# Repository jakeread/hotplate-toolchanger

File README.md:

## Hotplate Toolchanger 

This is the hardware (and firmware) repo for the hotplate, an automatic, fully printable toolchanger for cnc machines. It's ostensibly part of the [clank machine platform](https://clank.tools/tools), but you could probably stick it on anything. Or reference the design patterns, and stick the idea on anything. 

Read the [dev log](log/hotplate-log.md) for updates, and you can find the [most up to date CAD in /cad](cad). Associated circuits are in [/circuit](circuit) and their firmwares in [/firmware](firmware). Some of the firmware stuff is still private (submodules) so cloning might be troublesome at the moment, just download the zip. 

More extensive documentation is [online at clank.tools/tools](https://clank.tools/tools) !

This repo is mirrored [on github](https://github.com/jakeread/hotplate-toolchanger/) and the [cba internal gitlab](https://gitlab.cba.mit.edu/jakeread/hotplate-toolchanger/).

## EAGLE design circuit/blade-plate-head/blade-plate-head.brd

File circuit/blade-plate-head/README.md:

## Hotplate Blade Head 

This circuit is integrated on the toolchanger, it contains hardware to actuate a standard servo and connects to [OSAP](https://gitlab.cba.mit.edu/jakeread/osap) systems over the [UCBus](https://gitlab.cba.mit.edu/jakeread/ucbus) PHY. 

An eagle project is here in this folder...

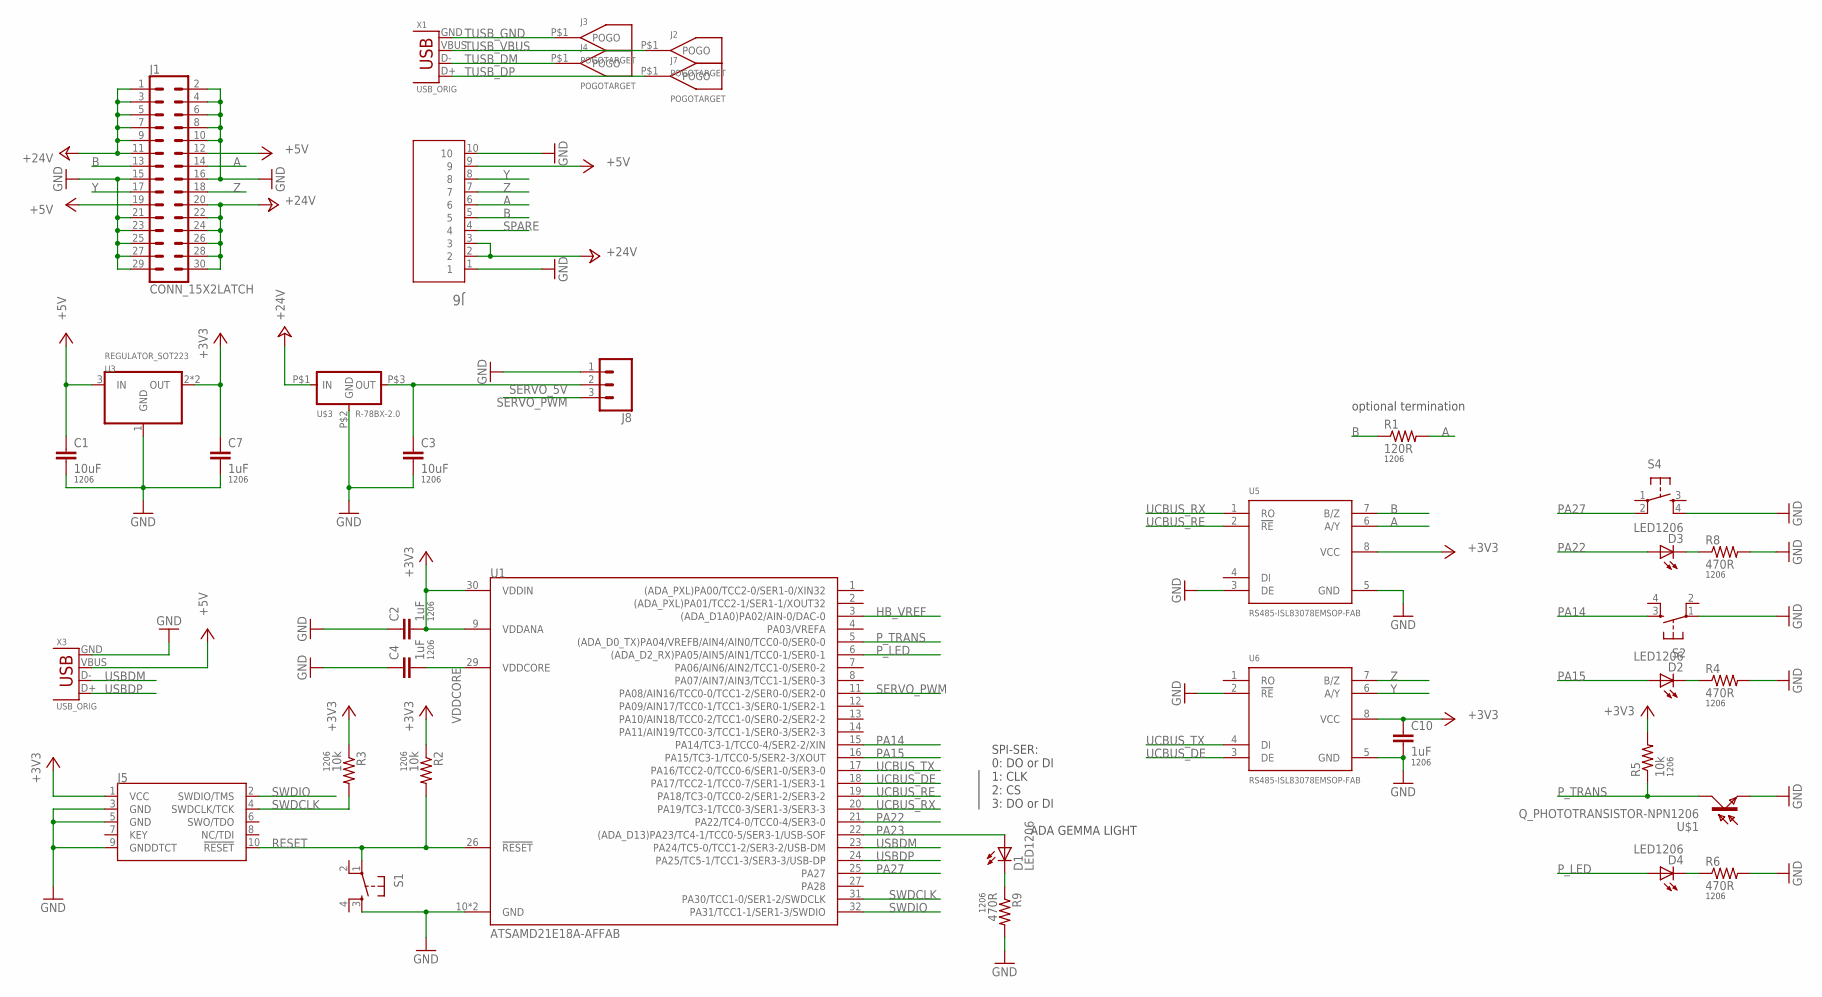
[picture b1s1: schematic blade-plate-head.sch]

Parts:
C1, C3: 10uF; 1206
C2, C4, C7, C10: 1uF; 1206
D1, D2, D3, D4: LED1206
J1: CONN_15X2LATCH; 2X15-SHROUDED_LATCH
J2, J3, J4, J7: POGOTARGET; POGO_TARGET
J5: CORTEX_JTAG_DEBUG_PTH_NS; 2X5-PTH-1.27MM-NO_SILK
J6: BLADE_10P_SCKT_1-1674231-1; TE_1-1674231-1
J8: CONN_03LOCK_NO_SILK; 1X03_LOCK_NO_SILK
R1: 120R; 1206
R2, R3, R5: 10k; 1206
R4, R6, R8, R9: 470R; 1206
S1, S2, S4: SW_SWITCH_TACTILE_6MM6MM_SWITCH; 6MM_SWITCH
U1: ATSAMD21E18A-AFFAB; TQFP-32-FAB
U3: REGULATOR_SOT223; SOT223
U5, U6: RS485-ISL83078EMSOP-FAB; 8-MSOP-FAB
U$1: Q_PHOTOTRANSISTOR-NPN1206; OP1206
U$3: R-78BX-2.0
X1, X3: USB_ORIG; DX4R005HJ5

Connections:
+3V3: C2.2, C7.1, C10.1, J5.1 (VCC), R2.1, R3.1, R5.2, U1.9 (VDDANA), U1.30 (VDDIN), U3.2 (OUT), U3.4 (OUT), U5.8 (VCC), U6.8 (VCC)
+5V: C1.1, J1.12, J1.19, J6.9, U3.3 (IN), X3.VBUS
+24V: J1.1, J1.3, J1.5, J1.7, J1.9, J1.11, J1.20, J1.22, J1.24, J1.26, J1.28, J1.30, J6.2, J6.3, U$3.P$1 (IN)
A: J1.14, J6.6, R1.2, U5.6 (A/Y)
B: J1.13, J6.5, R1.1, U5.7 (B/Z)
GND: C1.2, C2.1, C3.2, C4.1, C7.2, C10.2, J1.2, J1.4, J1.6, J1.8, J1.10, J1.15, J1.16, J1.21, J1.23, J1.25, J1.27, J1.29, J5.3 (GND), J5.5 (GND), J5.9 (GNDDTCT), J6.1, J6.10, J8.1, R4.2, R6.2, R8.2, R9.2, S1.3 (S), S2.1, S4.4 (S1), U1.10 (GND), U1.28 (GND), U3.1 (GND), U5.3 (DE), U5.5 (GND), U6.2 (!RE), U6.5 (GND), U$1.EMITTER (E), U$3.P$2 (GND), X3.GND
HB_VREF: U1.3 ((ADA_D1A0)PA02/AIN-0/DAC-0)
unnamed: D3.2 (C), R8.1
unnamed: D2.2 (C), R4.1
unnamed: D4.2 (C), R6.1
unnamed: D1.2 (C), R9.1
PA14: S2.3 (S), U1.15 (PA14/TC3-1/TCC0-4/SER2-2/XIN)
PA15: D2.1 (A), U1.16 (PA15/TC3-1/TCC0-5/SER2-3/XOUT)
PA22: D3.1 (A), U1.21 (PA22/TC4-0/TCC0-4/SER3-0)
PA23: D1.1 (A), U1.22 ((ADA_D13)PA23/TC4-1/TCC0-5/SER3-1/USB-S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)
PA27: S4.2 (P1), U1.25 (PA27)
P_LED: D4.1 (A), U1.6 ((ADA_D2_RX)PA05/AIN5/AIN1/TCC0-1/SER0-1)
P_TRANS: R5.1, U1.5 ((ADA_D0_TX)PA04/VREFB/AIN4/AIN0/TCC0-0/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), U$1.COLLECTOR (C)
RESET: J5.10 (!RESET), R2.2, S1.1, U1.26 (!RESET)
SERVO_5V: C3.1, J8.2, U$3.P$3 (OUT)
SERVO_PWM: J8.3, U1.11 (PA08/AIN16/TCC0-0/TCC1-2/SER0-0/SER2-0)
SPARE: J6.4
SWDCLK: J5.4 (SWDCLK/TCK), R3.2, U1.31 (PA30/TCC1-0/SER1-2/SWDCLK)
SWDIO: J5.2 (SWDIO/TMS), U1.32 (PA31/TCC1-1/SER1-3/SWDIO)
TUSB_DM: J4.P$1, X1.D-
TUSB_DP: J7.P$1, X1.D+
TUSB_GND: J3.P$1, X1.GND
TUSB_VBUS: J2.P$1, X1.VBUS
UCBUS_DE: U1.18 (PA17/TCC2-1/TCC0-7/SER1-1/SER3-1), U6.3 (DE)
UCBUS_RE: U1.19 (PA18/TC3-0/TCC0-2/SER1-2/SER3-2), U5.2 (!RE)
UCBUS_RX: U1.20 (PA19/TC3-1/TCC0-3/SER1-3/SER3-3), U5.1 (RO)
UCBUS_TX: U1.17 (PA16/TCC2-0/TCC0-6/SER1-0/SER3-0), U6.4 (DI)
USBDM: U1.23 (PA24/TC5-0/TCC1-2/SER3-2/USB-DM), X3.D-
USBDP: U1.24 (PA25/TC5-1/TCC1-3/SER3-3/USB-DP), X3.D+
VDDCORE: C4.2, U1.29 (VDDCORE)
Y: J1.17, J6.8, U6.6 (A/Y)
Z: J1.18, J6.7, U6.7 (B/Z)

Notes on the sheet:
SPI-SER: 0: DO or DI 1: CLK 2: CS 3: DO or DI
ADA GEMMA LIGHT
optional termination

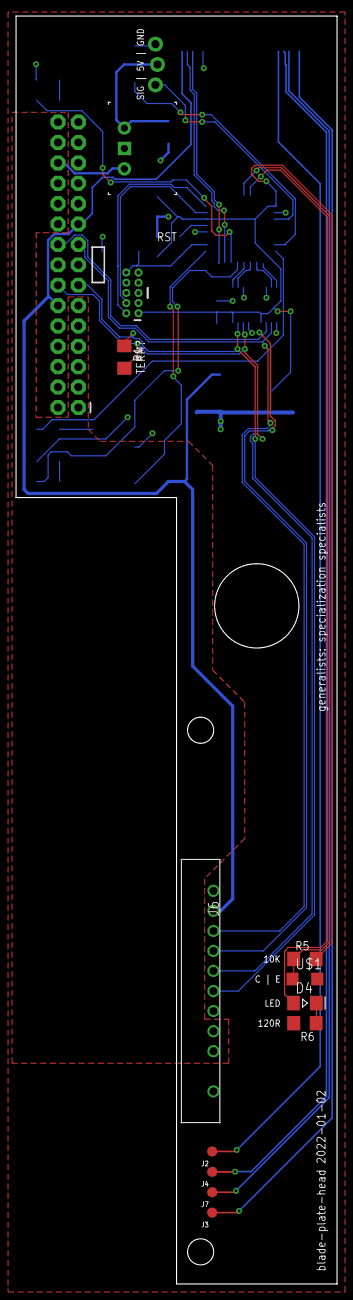
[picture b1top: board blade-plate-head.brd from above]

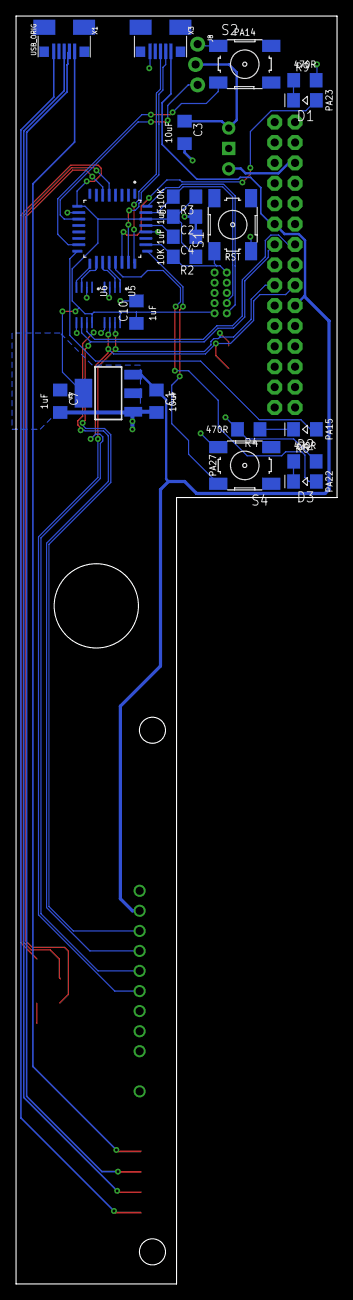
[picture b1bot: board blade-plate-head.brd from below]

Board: 2 copper layers, 40.0 x 158.0 mm, 37 parts (24 on the bottom side), 35 nets.

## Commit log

2022-01-28 blank slate hotplate

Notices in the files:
parts and their libraries:
SparkFun-Connectors: Licensing: Creative Commons ShareAlike 4.0 International - https://creativecommons.org/licenses/by-sa/4.0
